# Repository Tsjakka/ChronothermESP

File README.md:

# ChronothermESP
ESP C3 project for controlling the Honeywell Chronotherm III remotely.

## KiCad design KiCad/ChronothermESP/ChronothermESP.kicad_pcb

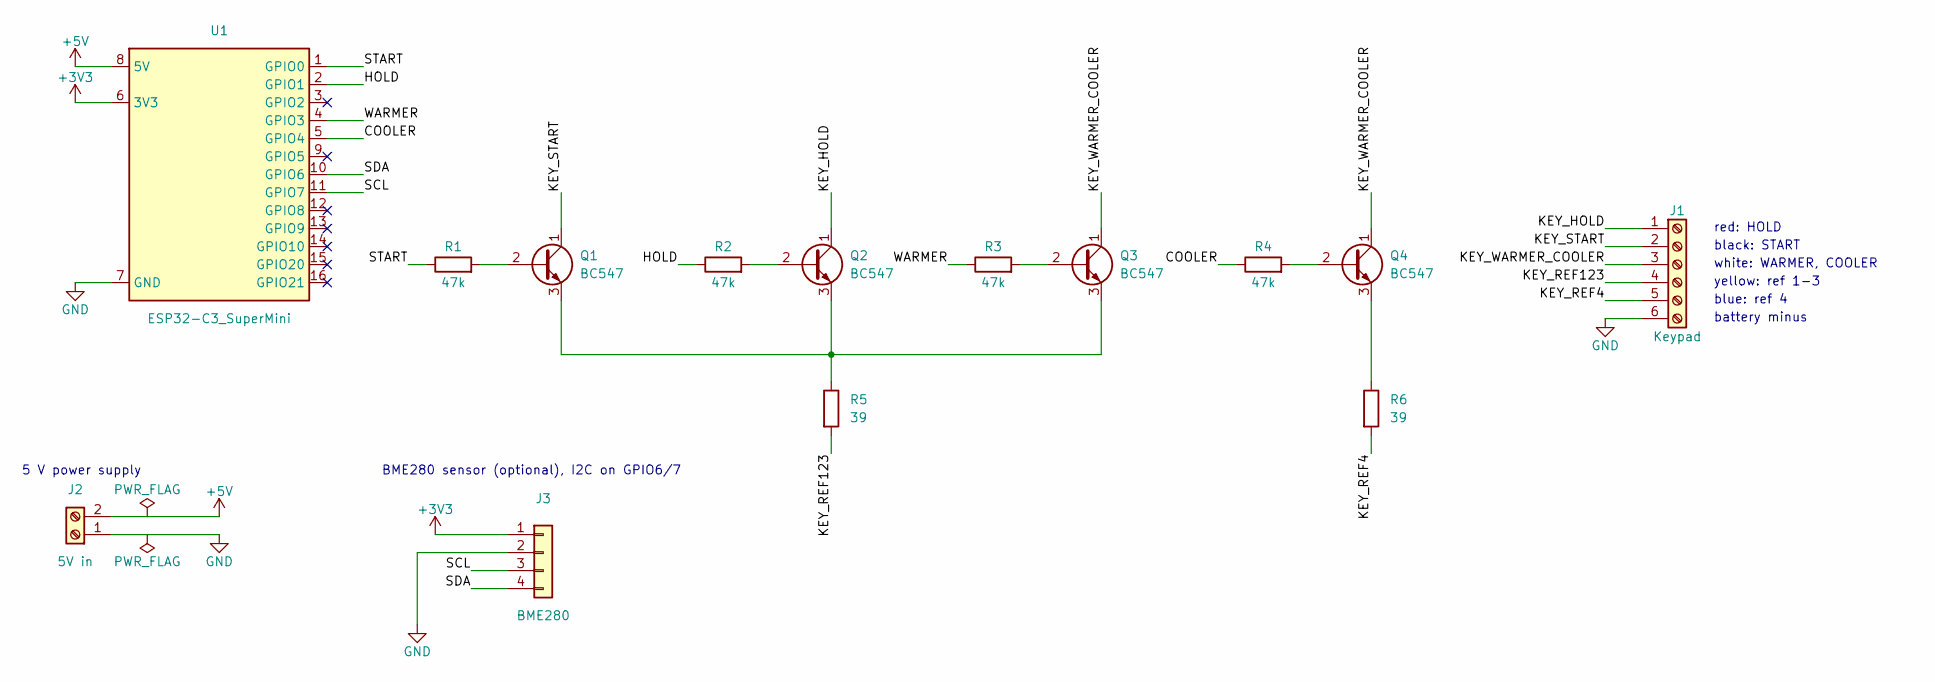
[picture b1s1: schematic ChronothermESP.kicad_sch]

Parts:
J1: Keypad; PhoenixContact_MC_1,5_6-G-3.81_1x06_P3.81mm_Horizontal
J2: 5V in; TerminalBlock_Phoenix_MKDS-1,5-2-5.08_1x02_P5.08mm_Horizont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
J3: BME280; PinHeader_1x04_P2.54mm_Vertical
Q1, Q2, Q3, Q4: BC547; TO-92_Inline
R1, R2, R3, R4: 47k; R_Axial_DIN0207_L6.3mm_D2.5mm_P10.16mm_Horizontal
R5, R6: 39; R_Axial_DIN0207_L6.3mm_D2.5mm_P10.16mm_Horizontal
U1: ESP32-C3_SuperMini

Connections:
+3V3: J3.1, U1.6 (3V3)
+5V: J2.2, U1.8 (5V)
/COOLER: R4.1, U1.5 (GPIO4)
/HOLD: R2.1, U1.2 (GPIO1)
/KEY_HOLD: J1.1, Q2.1 (C)
/KEY_REF4: J1.5, R6.2
/KEY_REF123: J1.4, R5.2
/KEY_START: J1.2, Q1.1 (C)
/KEY_WARMER_COOLER: J1.3, Q3.1 (C), Q4.1 (C)
/SCL: J3.3, U1.11 (GPIO7)
/SDA: J3.4, U1.10 (GPIO6)
/START: R1.1, U1.1 (GPIO0)
/WARMER: R3.1, U1.4 (GPIO3)
GND: J1.6, J2.1, J3.2, U1.7 (GND)
unnamed: Q1.2 (B), R1.2
unnamed: Q1.3 (E), Q2.3 (E), Q3.3 (E), R5.1
unnamed: Q2.2 (B), R2.2
unnamed: Q3.2 (B), R3.2
unnamed: Q4.2 (B), R4.2
unnamed: Q4.3 (E), R6.1

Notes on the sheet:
red: HOLD
black: START
white: WARMER, COOLER
yellow: ref 1-3
blue: ref 4
battery minus
5 V power supply
BME280 sensor (optional), I2C on GPIO6/7

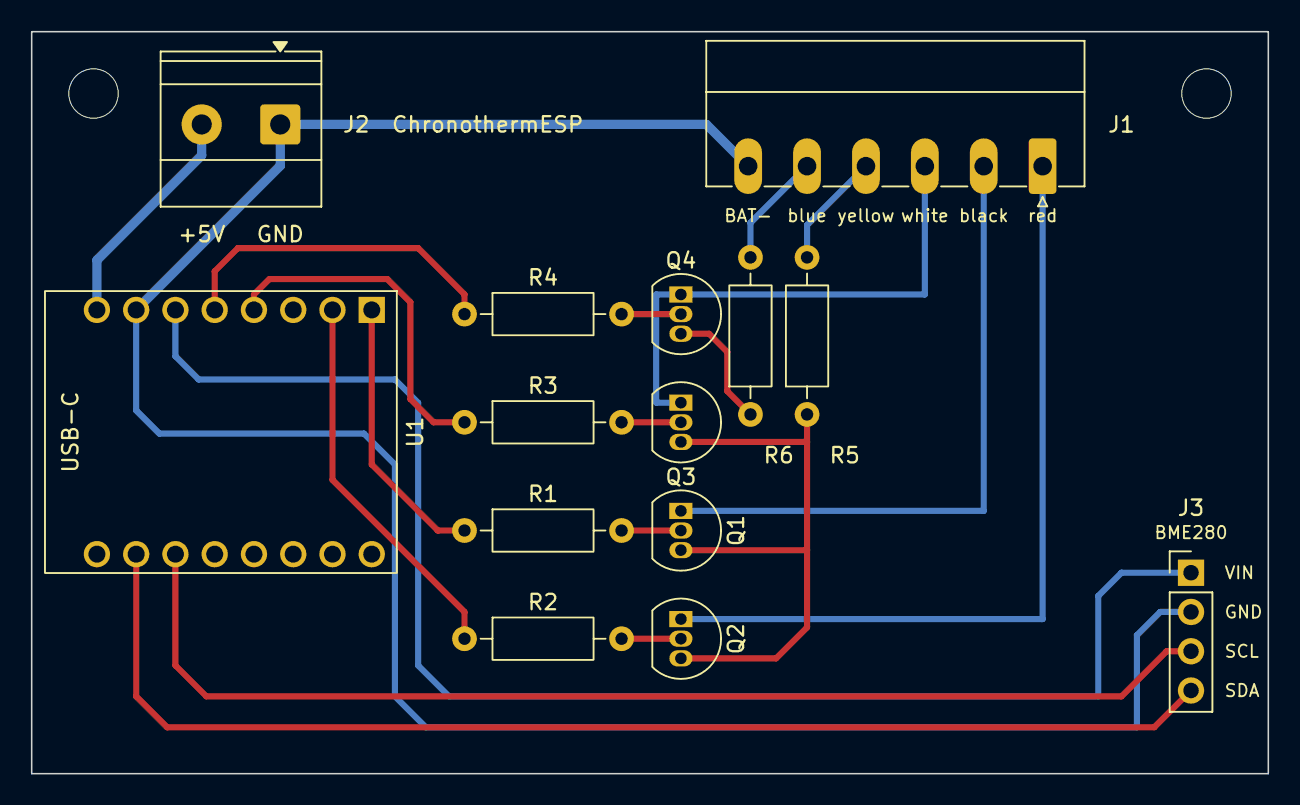
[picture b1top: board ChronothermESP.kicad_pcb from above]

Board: 2 copper layers, 80.0 x 48.0 mm, 16 parts (0 on the bottom side), 20 nets.

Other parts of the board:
H1, H2: MountingHole_3.2mm_M3

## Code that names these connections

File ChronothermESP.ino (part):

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// Button commands (GPIO pins)
const int START_PROGRAM = 0;
const int HOLD_TEMP = 1;
const int WARMER = 3;
const int COOLER = 4;
// ************************************************************************
// Change the constants above to adjust the software to your situation
// ************************************************************************

// Timing
const int HOLD_TIME = 300;   // ms to hold a keypress
const int IDLE_TIME = 600;   // ms between keypresses

// Temperature limits of Chronotherm III
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  // Initialize pins
  pinMode(START_PROGRAM, OUTPUT);
  pinMode(HOLD_TEMP, OUTPUT);
  pinMode(WARMER, OUTPUT);
  pinMode(COOLER, OUTPUT);

  digitalWrite(START_PROGRAM, LOW);
  digitalWrite(HOLD_TEMP, LOW);
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
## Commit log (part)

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2026-05-26 Initial commit.
2026-05-26 Added missing multi-line comment.
2026-06-03 Reworked imap part using Codex.
2026-06-09 Used Codex to come up with a stable implementation.

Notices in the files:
ChronothermESP.ino:
BSD license, this line and all text above must be included in any redistribution.
